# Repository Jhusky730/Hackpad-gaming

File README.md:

# Hackpad-gaming
This is my hackpad. It consists of a 3x3 key matrix with RGB LEDs, an OLED screen, and a rotary encoder.

Model of hackpad:

Screenshot of Shematic for PCB:

Screenshot of PCB:

Layers of the keyboard:

Top side of both parts:

The cases act as a clamp and ledge for the pcb to hold it in place:

Bill Of Materials: 
1x Seeed XIAO RP2040  
1x 0.91" OLED9x MX style 1u switches  
9x white blank DSA keycaps  
9x SK6812 Mini-E LEDs  
10x 1N4148 DO-35 Diodes  
1x EC11E Rotary Encoder (With Push Button)  
1x Top case(3D printed)  
1x Middle case(3D printed)  
1x Bottom case(3D printed)  
4x M3x5mx4mm heatset inserts  
4x M3x6mm screws (I will buy these)

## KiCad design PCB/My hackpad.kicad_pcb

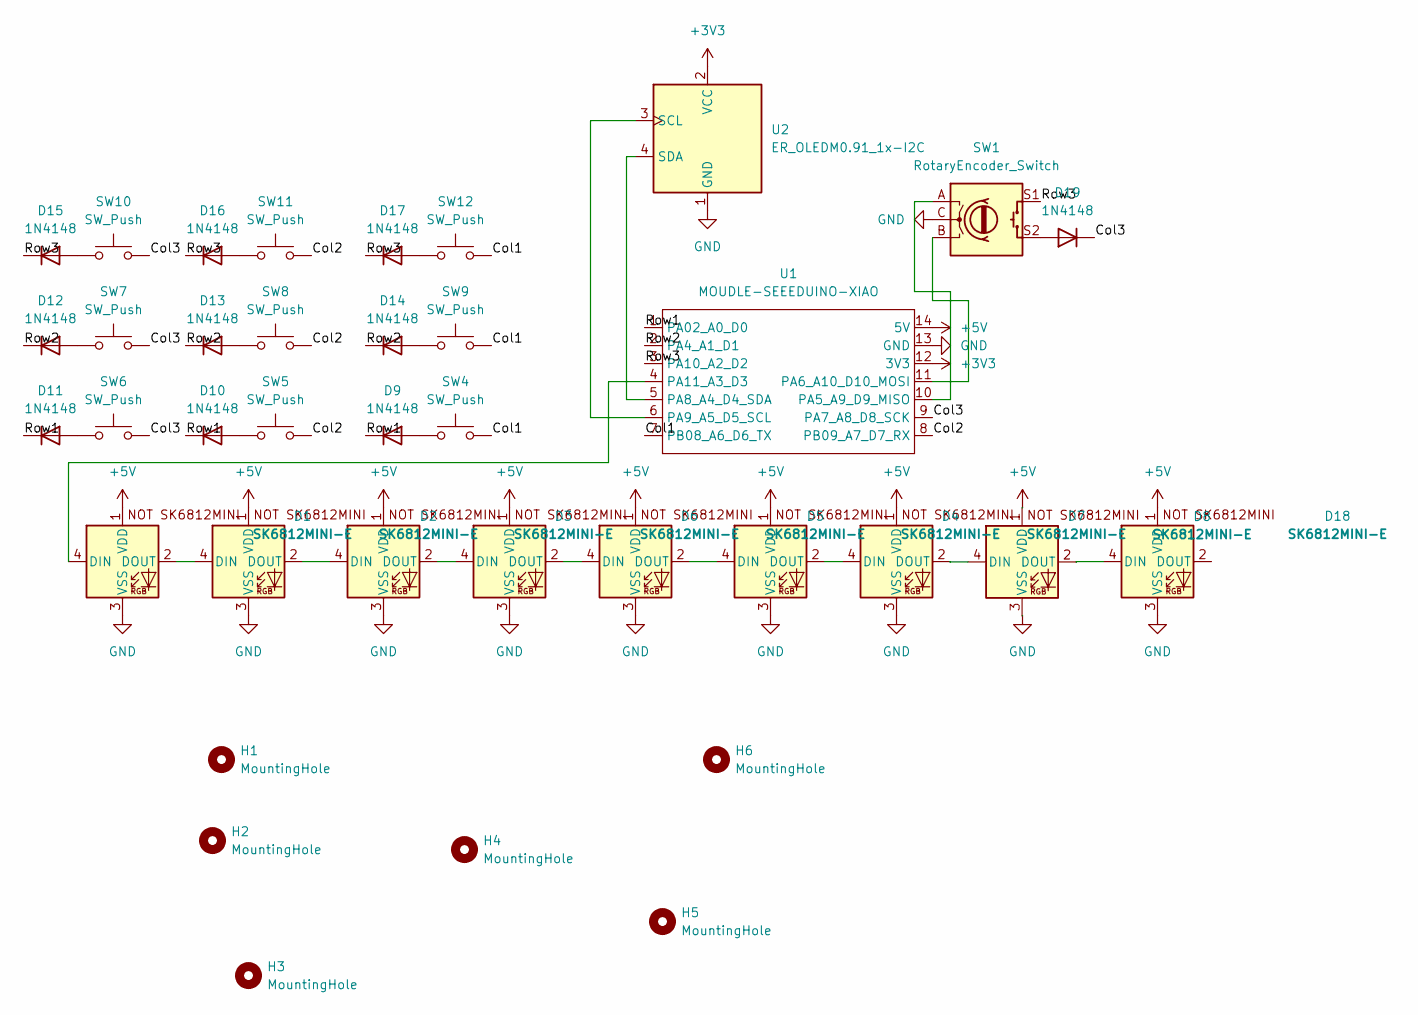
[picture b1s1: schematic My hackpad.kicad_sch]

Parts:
D1, D2, D3, D4, D5, D6, D7, D8, D18: SK6812MINI-E; SK6812MINI-E_fixed
D9, D10, D11, D12, D13, D14, D15, D16, D17, D19: 1N4148; D_DO-35_SOD27_P7.62mm_Horizontal
H1, H2, H3, H4, H5, H6: MountingHole; MountingHole_3.2mm_M3
SW1: RotaryEncoder_Switch; RotaryEncoder_Alps_EC11E-Switch_Vertical_H20mm_CircularMoun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
SW4, SW5, SW6, SW7, SW8, SW9, SW10, SW11, SW12: SW_Push; SW_Cherry_MX_PCB_1.00u
U1: MOUDLE-SEEEDUINO-XIAO; XIAO-Generic-Hybrid-14P-2.54-21X17.8MM
U2: ER_OLEDM0.91_1x-I2C

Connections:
+3V3: U1.12 (3V3), U2.2 (VCC)
+5V: D1.1 (VDD), D2.1 (VDD), D3.1 (VDD), D4.1 (VDD), D5.1 (VDD), D6.1 (VDD), D7.1 (VDD), D8.1 (VDD), D18.1 (VDD), U1.14 (5V)
/Col1: SW4.2, SW9.2, SW12.2, U1.7 (PB08_A6_D6_TX)
/Col2: SW5.2, SW8.2, SW11.2, U1.8 (PB09_A7_D7_RX)
/Col3: D19.1 (K), SW6.2, SW7.2, SW10.2, U1.9 (PA7_A8_D8_SCK)
/Row1: D9.1 (K), D10.1 (K), D11.1 (K), U1.1 (PA02_A0_D0)
/Row2: D12.1 (K), D13.1 (K), D14.1 (K), U1.2 (PA4_A1_D1)
/Row3: D15.1 (K), D16.1 (K), D17.1 (K), SW1.S1, U1.3 (PA10_A2_D2)
GND: D1.3 (VSS), D2.3 (VSS), D3.3 (VSS), D4.3 (VSS), D5.3 (VSS), D6.3 (VSS), D7.3 (VSS), D8.3 (VSS), D18.3 (VSS), SW1.C, U1.13 (GND), U2.1 (GND)
unnamed: D1.4 (DIN), U1.4 (PA11_A3_D3)
unnamed: D1.2 (DOUT), D2.4 (DIN)
unnamed: D2.2 (DOUT), D3.4 (DIN)
unnamed: D3.2 (DOUT), D6.4 (DIN)
unnamed: D4.4 (DIN), D5.2 (DOUT)
unnamed: D4.2 (DOUT), D7.4 (DIN)
unnamed: D5.4 (DIN), D6.2 (DOUT)
unnamed: D7.2 (DOUT), D8.4 (DIN)
unnamed: D9.2 (A), SW4.1
unnamed: D10.2 (A), SW5.1
unnamed: D11.2 (A), SW6.1
unnamed: D12.2 (A), SW7.1
unnamed: D13.2 (A), SW8.1
unnamed: D14.2 (A), SW9.1
unnamed: D15.2 (A), SW10.1
unnamed: D16.2 (A), SW11.1
unnamed: D17.2 (A), SW12.1
unnamed: D8.2 (DOUT), D18.4 (DIN)
unnamed: D19.2 (A), SW1.S2
unnamed: SW1.A, U1.10 (PA5_A9_D9_MISO)
unnamed: SW1.B, U1.11 (PA6_A10_D10_MOSI)
unnamed: U1.5 (PA8_A4_D4_SDA), U2.4 (SDA)
unnamed: U1.6 (PA9_A5_D5_SCL), U2.3 (SCL)

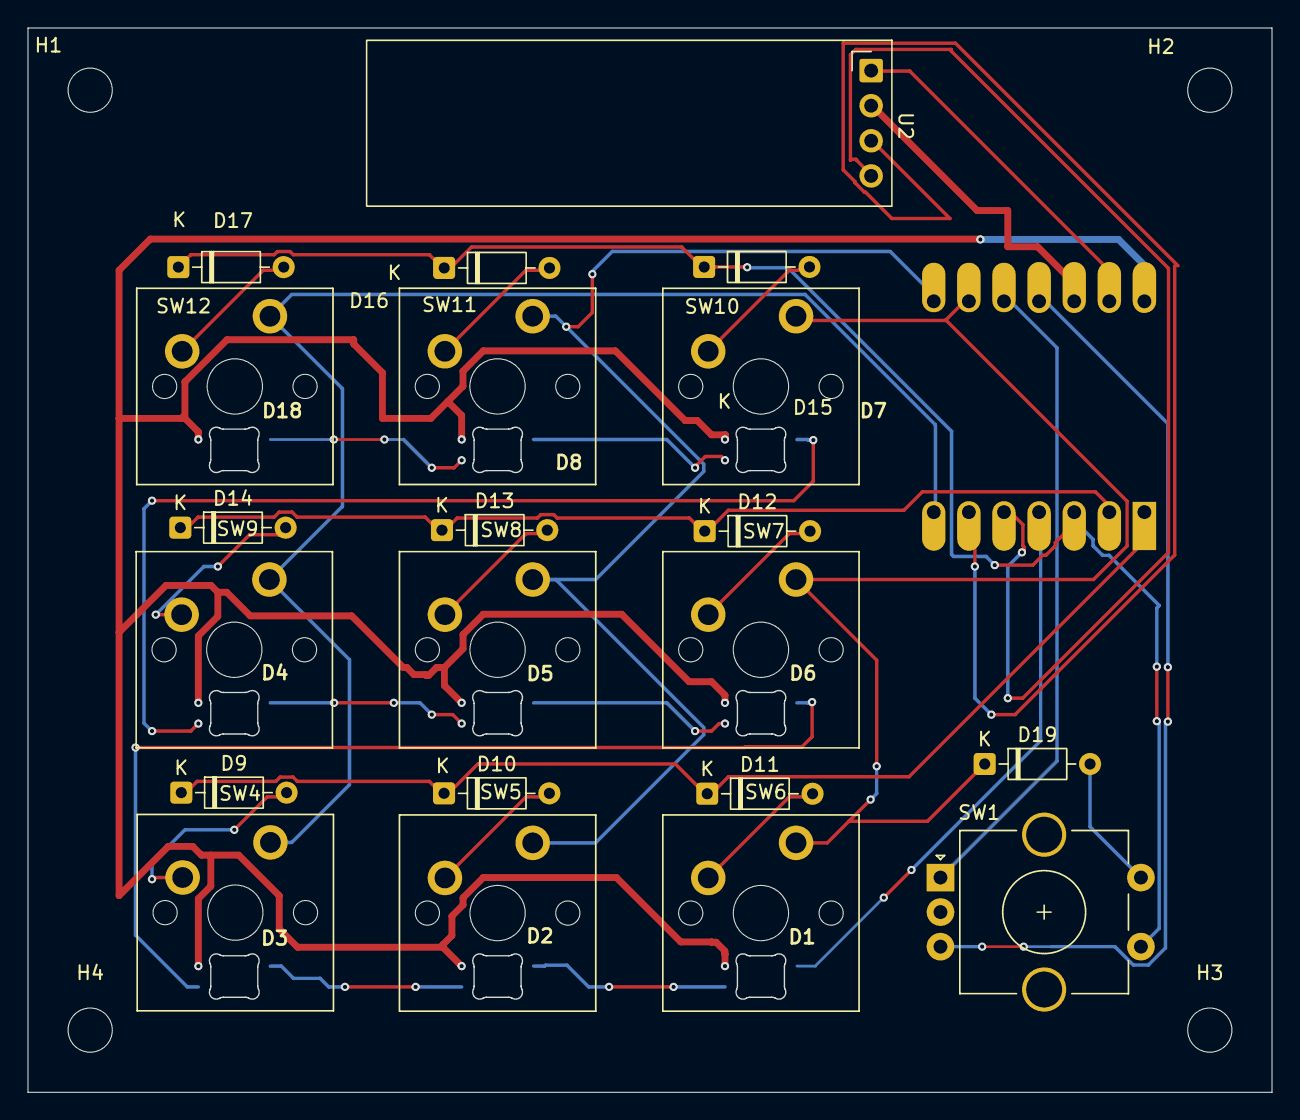
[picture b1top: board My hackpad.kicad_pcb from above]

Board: 2 copper layers, 89.9 x 77.0 mm, 35 parts (1 on the bottom side), 32 nets.

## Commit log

2026-06-15 Include model image in README
    Added a model image of the hackpad to the README.
2026-06-15 Fix formatting in README description
2026-06-15 Update README.md to fix newline in description
    Fixed formatting issue by removing newline character.
2026-06-15 Update README with images and descriptions
    Added images and descriptions for hackpad components.
2026-06-15 Add Bill of Materials to README
    Added a Bill of Materials section with components list.
2026-06-15 Adjust image tags for responsive design in README
    Updated image tags in README to use 100% width for better responsiveness.
2026-06-15 Revise Bill Of Materials formatting in README
    Updated the Bill Of Materials section for clarity and formatting.
2026-06-16 Update README with note on M3x6mm screws purchase
